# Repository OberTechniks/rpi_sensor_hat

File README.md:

# rpi_sensor_hat
Sensor hat for Raspberry Pi 4 Model B

kicad: version 5.1.8
stm32: STM32CubeIDE Version: 1.5.1

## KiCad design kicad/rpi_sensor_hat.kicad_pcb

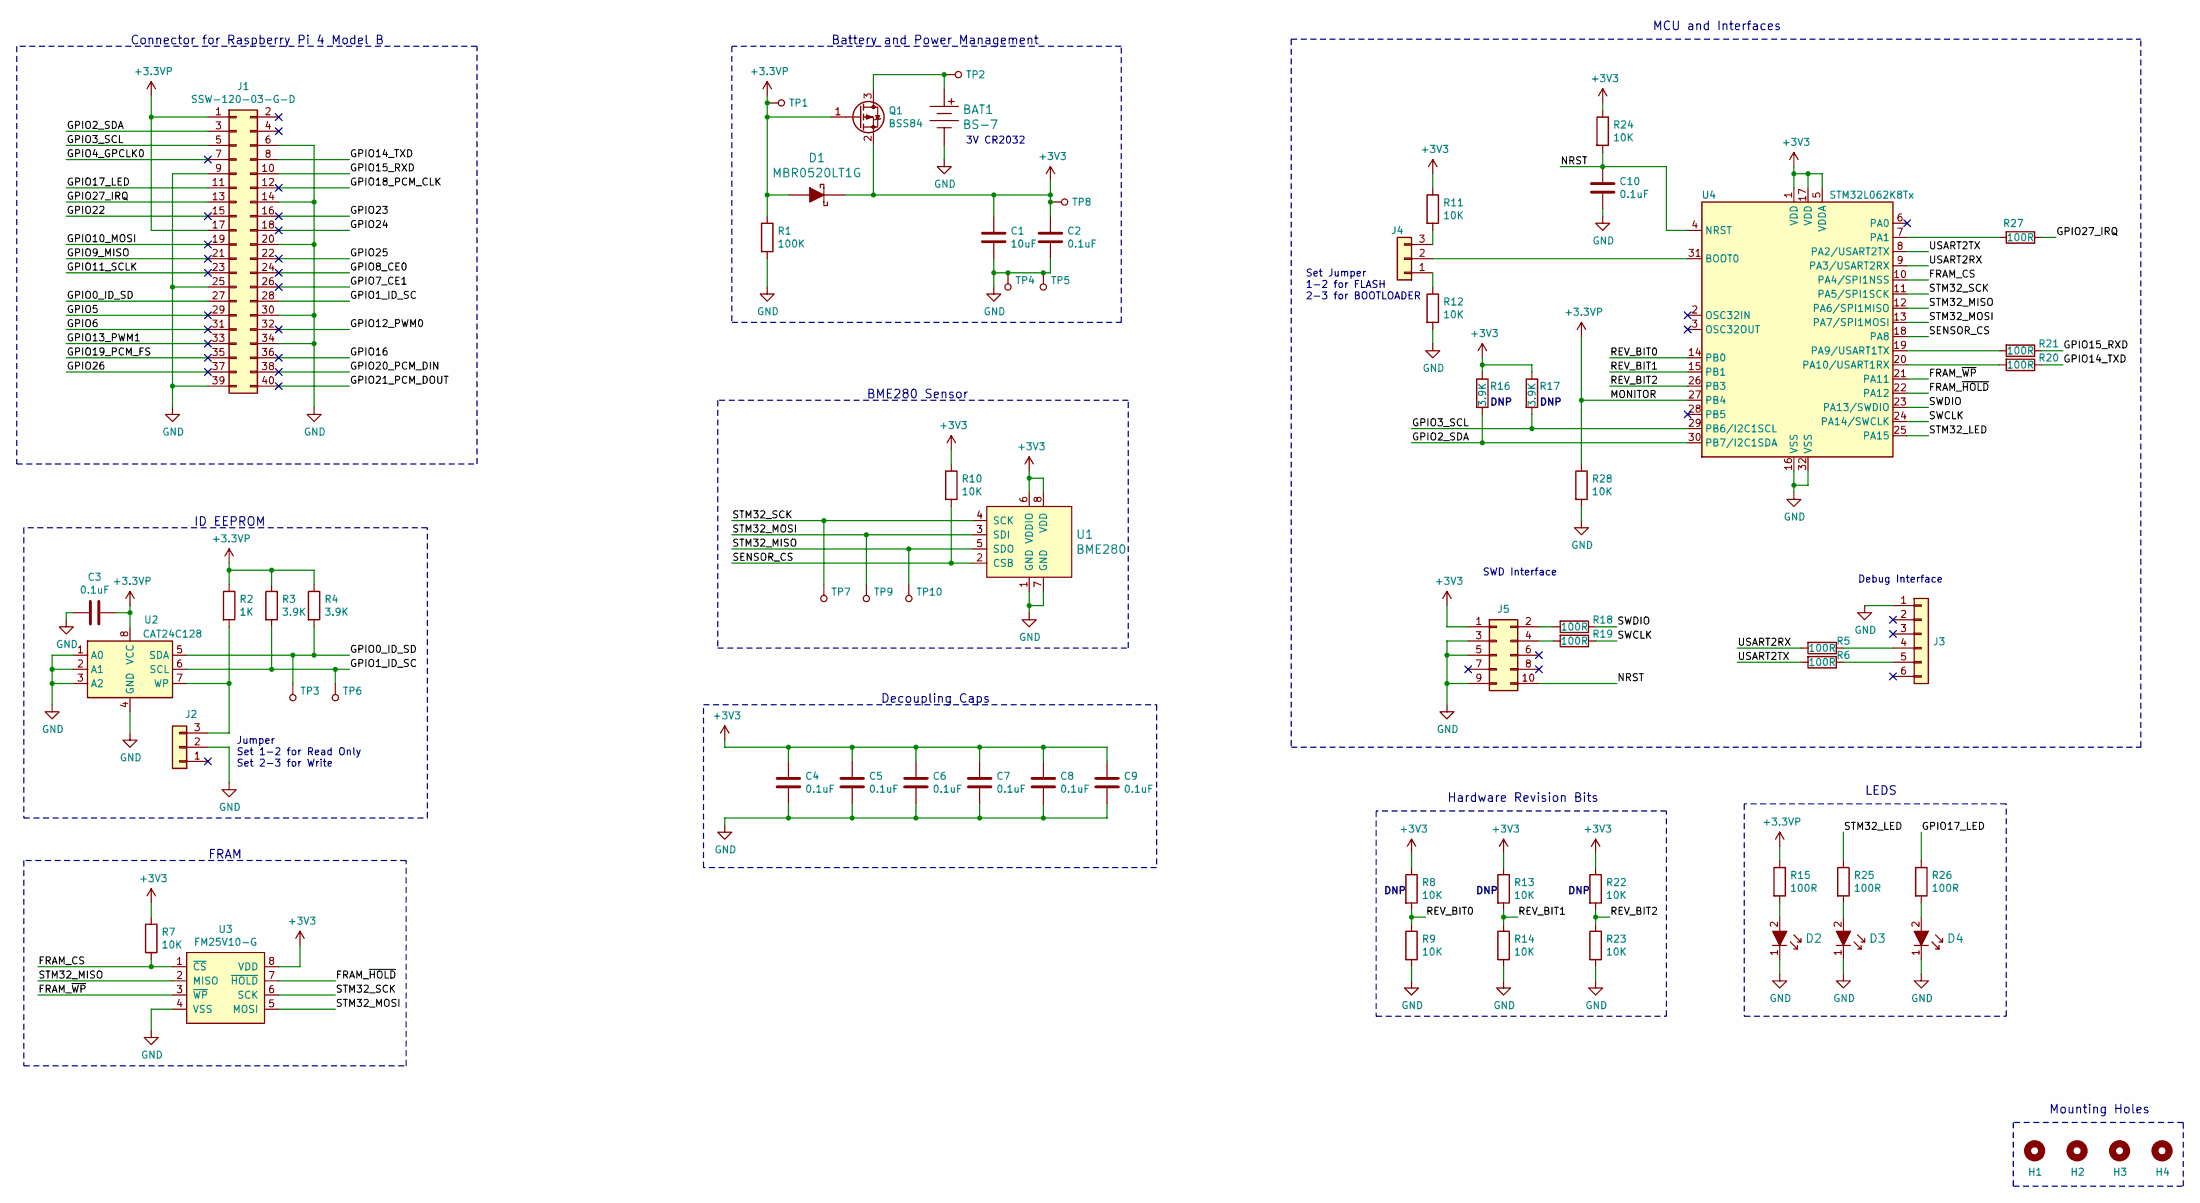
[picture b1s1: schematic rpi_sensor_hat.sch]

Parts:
BAT1: BS-7; Battery_Holder_Coin_2032_BS-7; MPN BS-7; Digi-Key_PN BS-7-ND
C1: 10uF; C_0805_2012Metric; MPN TMK212BBJ106KG-T
C2, C3, C4, C5, C6, C7, C8, C9, C10: 0.1uF; C_0805_2012Metric; MPN 08055C104KAT2A
D1: MBR0520LT1G; SOD-123; MPN MBR0520LT1G; Digi-Key_PN MBR0520LT1GOSCT-ND
D2, D3, D4: LG_R971-KN-1; LED_0805_2012Metric; MPN LG R971-KN-1; Digi-Key_PN 475-1410-1-ND
H1, H2, H3, H4: MountingHole; MountingHole_2.7mm_M2.5
J1: SSW-120-03-G-D; ssw-120-03-g-d
J2, J4: Conn_01x03; PinHeader_1x03_P2.54mm_Vertical; MPN TSW-103-07-F-S
J3: Conn_01x06; PinHeader_1x06_P2.54mm_Vertical; MPN 61300611121
J5: Conn_02x05_Odd_Even; PinHeader_2x05_P1.27mm_Vertical_SMD; MPN FTSH-105-01-L-DV-K
Q1: BSS84; SOT-23; MPN BSS84-7-F
R1: 100K; R_0805_2012Metric; MPN RC0805JR-07100KL
R2: 1K; R_0805_2012Metric; MPN RC0805FR-071KL
R3, R4, R16, R17: 3.9K; R_0805_2012Metric; MPN RC0805FR-073K9L
R5, R6, R15, R18, R19, R20, R21, R25, R26, R27: 100R; R_0805_2012Metric; MPN RC0805FR-07100RL
R7, R8, R9, R10, R11, R12, R13, R14, R22, R23, R24, R28: 10K; R_0805_2012Metric; MPN RC0805JR-0710KL
TP1, TP2, TP3, TP4, TP5, TP6, TP7, TP8, TP9, TP10: 5016; TestPoint_Pad_1.0x1.0mm; MPN 5016; Digi-Key_PN 36-5016CT-ND
U1: BME280; Pressure_Sensor_LGA-8_2.5x2.5mm_BME280; MPN BME280; Digi-Key_PN 828-1063-1-ND
U2: CAT24C128; SOIC-8_3.9x4.9mm_P1.27mm; MPN CAT24C128WI-GT3
U3: FM25V10-G; SOIC-8_3.9x4.9mm_P1.27mm; MPN FM25V10-G
U4: STM32L062K8Tx; LQFP-32_7x7mm_P0.8mm; MPN STM32L062K8T6

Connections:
+3.3VP: C3.1, D1.A, J1.1, J1.17, Q1.1 (G), R1.1, R2.1, R3.1, R4.1, R15.1, R28.1, TP1.1, U2.8 (VCC), U4.27 (PB4)
+3V3: C1.1, C2.1, C4.1, C5.1, C6.1, C7.1, C8.1, C9.1, D1.K, J5.1, Q1.2 (S), R7.1, R8.1, R10.1, R11.1, R13.1, R16.1, R17.1, R22.1, R24.1, TP8.1, U1.6 (VDDIO), U1.8 (VDD), U3.8 (VDD), U4.1 (VDD), U4.5 (VDDA), U4.17 (VDD)
/FRAM_CS: R7.2, U3.1 (~CS), U4.10 (PA4/SPI1NSS)
/FRAM_~HOLD: U3.7 (~HOLD), U4.22 (PA12)
/FRAM_~WP: U3.3 (~WP), U4.21 (PA11)
/GPIO0_ID_SD: J1.27, R4.2, TP3.1, U2.5 (SDA)
/GPIO1_ID_SC: J1.28, R3.2, TP6.1, U2.6 (SCL)
/GPIO2_SDA: J1.3, R16.2, U4.30 (PB7/I2C1SDA)
/GPIO3_SCL: J1.5, R17.2, U4.29 (PB6/I2C1SCL)
/GPIO4_GPCLK0: J1.7
/GPIO5: J1.29
/GPIO6: J1.31
/GPIO7_CE1: J1.26
/GPIO8_CE0: J1.24
/GPIO9_MISO: J1.21
/GPIO10_MOSI: J1.19
/GPIO11_SCLK: J1.23
/GPIO12_PWM0: J1.32
/GPIO13_PWM1: J1.33
/GPIO14_TXD: J1.8, R21.1
/GPIO15_RXD: J1.10, R20.1
/GPIO16: J1.36
/GPIO17_LED: J1.11, R26.1
/GPIO18_PCM_CLK: J1.12
/GPIO19_PCM_FS: J1.35
/GPIO20_PCM_DIN: J1.38
/GPIO21_PCM_DOUT: J1.40
/GPIO22: J1.15
/GPIO23: J1.16
/GPIO24: J1.18
/GPIO25: J1.22
/GPIO26: J1.37
/GPIO27_IRQ: J1.13, R27.1
/NRST: C10.1, J5.10, R24.2, U4.4 (NRST)
/REV_BIT0: R8.2, R9.1, U4.14 (PB0)
/REV_BIT1: R13.2, R14.1, U4.15 (PB1)
/REV_BIT2: R22.2, R23.1, U4.26 (PB3)
/SENSOR_CS: R10.2, U1.2 (CSB), U4.18 (PA8)
/STM32_LED: R25.1, U4.25 (PA15)
/STM32_MISO: TP10.1, U1.5 (SDO), U3.2 (MISO), U4.12 (PA6/SPI1MISO)
/STM32_MOSI: TP9.1, U1.3 (SDI), U3.5 (MOSI), U4.13 (PA7/SPI1MOSI)
/STM32_SCK: TP7.1, U1.4 (SCK), U3.6 (SCK), U4.11 (PA5/SPI1SCK)
/SWCLK: R19.1, U4.24 (PA14/SWCLK)
/SWDIO: R18.1, U4.23 (PA13/SWDIO)
/USART2RX: R5.2, U4.9 (PA3/USART2RX)
/USART2TX: R6.2, U4.8 (PA2/USART2TX)
GND: BAT1.Neg, C1.2, C2.2, C3.2, C4.2, C5.2, C6.2, C7.2, C8.2, C9.2, C10.2, D2.1, D3.1, D4.1, J1.6, J1.9, J1.14, J1.20, J1.25, J1.30, J1.34, J1.39, J2.2, J3.1, J5.3, J5.5, J5.9, R1.2, R9.2, R12.2, R14.2, R23.2, R28.2, TP4.1, TP5.1, U1.1 (GND), U1.7 (GND), U2.1 (A0), U2.2 (A1), U2.3 (A2), U2.4 (GND), U3.4 (VSS), U4.16 (VSS), U4.32 (VSS)
unnamed: BAT1.Pos, Q1.3 (D), TP2.1
unnamed: D2.2, R15.2
unnamed: D3.2, R25.2
unnamed: D4.2, R26.2
unnamed: J2.3, R2.2, U2.7 (WP)
unnamed: J3.4, R5.1
unnamed: J3.5, R6.1
unnamed: J4.1, R12.1
unnamed: J4.2, U4.31 (BOOT0)
unnamed: J4.3, R11.2
unnamed: J5.2, R18.2
unnamed: J5.4, R19.2
unnamed: R20.2, U4.19 (PA9/USART1TX)
unnamed: R21.2, U4.20 (PA10/USART1RX)
unnamed: R27.2, U4.7 (PA1)

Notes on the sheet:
Connector for Raspberry Pi 4 Model B
Battery and Power Management
3V CR2032
Jumper Set 1-2 for Read Only Set 2-3 for Write
ID EEPROM
FRAM
BME280 Sensor
Decoupling Caps
DNP
Mounting Holes
Hardware Revision Bits
Set Jumper 1-2 for FLASH 2-3 for BOOTLOADER
SWD Interface
Debug Interface
MCU and Interfaces
LEDS

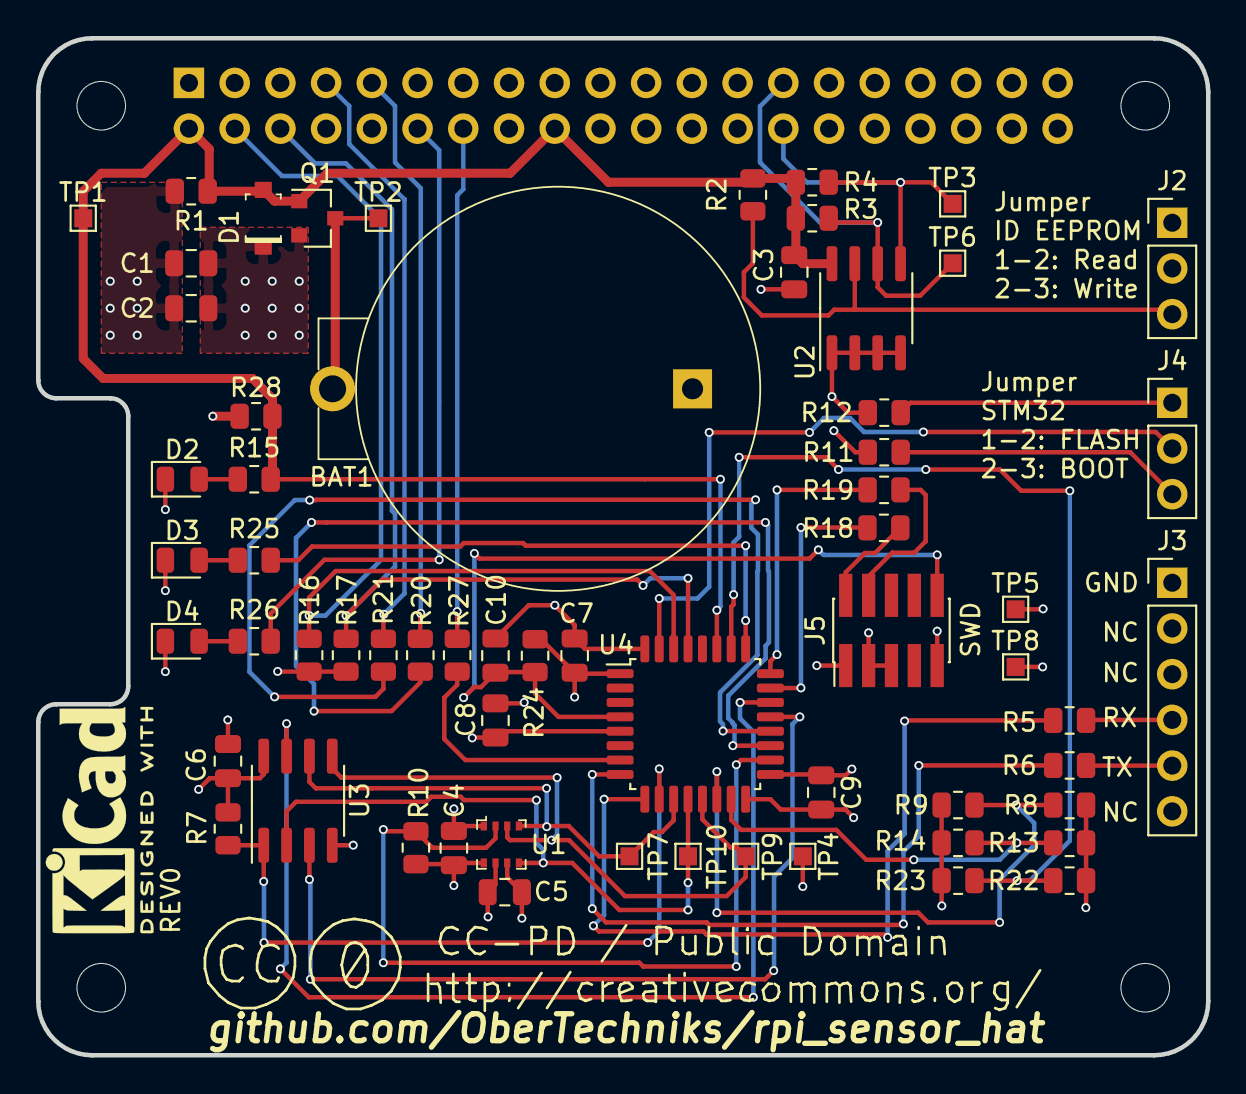
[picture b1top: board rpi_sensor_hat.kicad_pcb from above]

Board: 4 copper layers, 65.0 x 56.5 mm, 67 parts (1 on the bottom side), 42 nets.

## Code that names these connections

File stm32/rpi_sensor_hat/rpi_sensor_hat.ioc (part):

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Mcu.Name=STM32L062K8Tx
Mcu.Package=LQFP32
Mcu.UserName=STM32L062K8Tx
PA0.GPIOParameters=GPIO_PuPd
PA0.GPIO_PuPd=GPIO_PULLDOWN
PA0.Signal=GPIO_Input
PA1.GPIOParameters=GPIO_PuPd,GPIO_Label
PA1.GPIO_Label=GPIO27_IRQ
PA1.GPIO_PuPd=GPIO_PULLDOWN
PA1.Signal=GPIO_Input
PA10.Mode=Asynchronous
PA10.Signal=USART1_RX
PA11.GPIOParameters=PinState,GPIO_Label
PA11.GPIO_Label=FRAM_WP
PA11.PinState=GPIO_PIN_SET
PA11.Signal=GPIO_Output
PA12.GPIOParameters=PinState,GPIO_Label
PA12.GPIO_Label=FRAM_HOLD
PA12.PinState=GPIO_PIN_SET
PA12.Signal=GPIO_Output
PA13.Mode=Serial_Wire
PA13.Signal=SYS_SWDIO
PA14.Mode=Serial_Wire
PA14.Signal=SYS_SWCLK
PA15.GPIOParameters=GPIO_Label
PA15.GPIO_Label=LED
PA15.Signal=GPIO_Output
PA2.Mode=Asynchronous
PA2.Signal=USART2_TX
PA3.Mode=Asynchronous
PA3.Signal=USART2_RX
PA4.GPIOParameters=PinState,GPIO_Label
PA4.GPIO_Label=FRAM_CS
PA4.PinState=GPIO_PIN_SET
PA4.Signal=GPIO_Output
PA5.Mode=Full_Duplex_Master
PA5.Signal=SPI1_SCK
PA6.Mode=Full_Duplex_Master
PA6.Signal=SPI1_MISO
PA7.Mode=Full_Duplex_Master
PA7.Signal=SPI1_MOSI
PA8.GPIOParameters=PinState,GPIO_Label
PA8.GPIO_Label=SENSOR_CS
PA8.PinState=GPIO_PIN_SET
PA8.Signal=GPIO_Output
PA9.Mode=Asynchronous
PA9.Signal=USART1_TX
PB0.GPIOParameters=GPIO_Label
PB0.GPIO_Label=REV_BIT0
PB0.Signal=GPIO_Input
PB1.GPIOParameters=GPIO_Label
PB1.GPIO_Label=REV_BIT1
PB1.Signal=GPIO_Input
PB3.GPIOParameters=GPIO_Label
PB3.GPIO_Label=REV_BIT2
PB3.Signal=GPIO_Input
PB4.GPIOParameters=GPIO_Label
PB4.GPIO_Label=VMONITOR
PB4.Signal=GPIO_Input
PB5.GPIOParameters=GPIO_PuPd
PB5.GPIO_PuPd=GPIO_PULLDOWN
PB5.Signal=GPIO_Input
PB6.Mode=I2C
PB6.Signal=I2C1_SCL
PB7.Mode=I2C
PB7.Signal=I2C1_SDA
PC14-OSC32_IN.GPIOParameters=GPIO_PuPd
PC14-OSC32_IN.GPIO_PuPd=GPIO_PULLDOWN
PC14-OSC32_IN.Signal=GPIO_Input
PC15-OSC32_OUT.GPIOParameters=GPIO_PuPd
PC15-OSC32_OUT.GPIO_PuPd=GPIO_PULLDOWN
PC15-OSC32_OUT.Signal=GPIO_Input
RCC.SYSCLKFreq_VALUE=1048000
board=custom

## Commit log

2020-12-27 no message
2020-12-27 Create LICENSE
2020-12-28 Added STM32 microcontroller and FRAM non-volatile memory.
2020-12-28 Aded BME280 sensor.
2020-12-29 Added battery and power management.
2020-12-29 Finished schematic rev 0.
2020-12-30 Completed rev 0 of PCB layout.
2020-12-30 Gerbers ready for order.
2020-12-30 Generated gerbers and 3D STEP file.
2021-01-10 Initial commit of STM32 firmware.
2021-01-11 Blinky complete, printf working with local UART
2023-03-04 Data
